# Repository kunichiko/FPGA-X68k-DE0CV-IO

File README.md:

# FPGA-X68k I/O Board for DE0-CV

詳しい使い方は [Wiki](https://github.com/kunichiko/FPGA-X68k-DE0CV-IO/wiki) を参照してください。

# License

This repository is published under CC BY-NC (Creative Commons Attribution-NonCommercial 4.0 International Public License).

本リポジトリはクリエイティブコモンズの CC BY-NC ライセンスの元に公開します。

本リポジトリには私が作成したもの以外に、第三者が権利を持つソフトウェア等(PCBフットプリントライブラリなど)が含まれています。CC BY-NCライセンスの元で再頒布しても問題がないように注意しておりますが、もし頒布条件などが満たされないものが含まれていた場合はご連絡ください。

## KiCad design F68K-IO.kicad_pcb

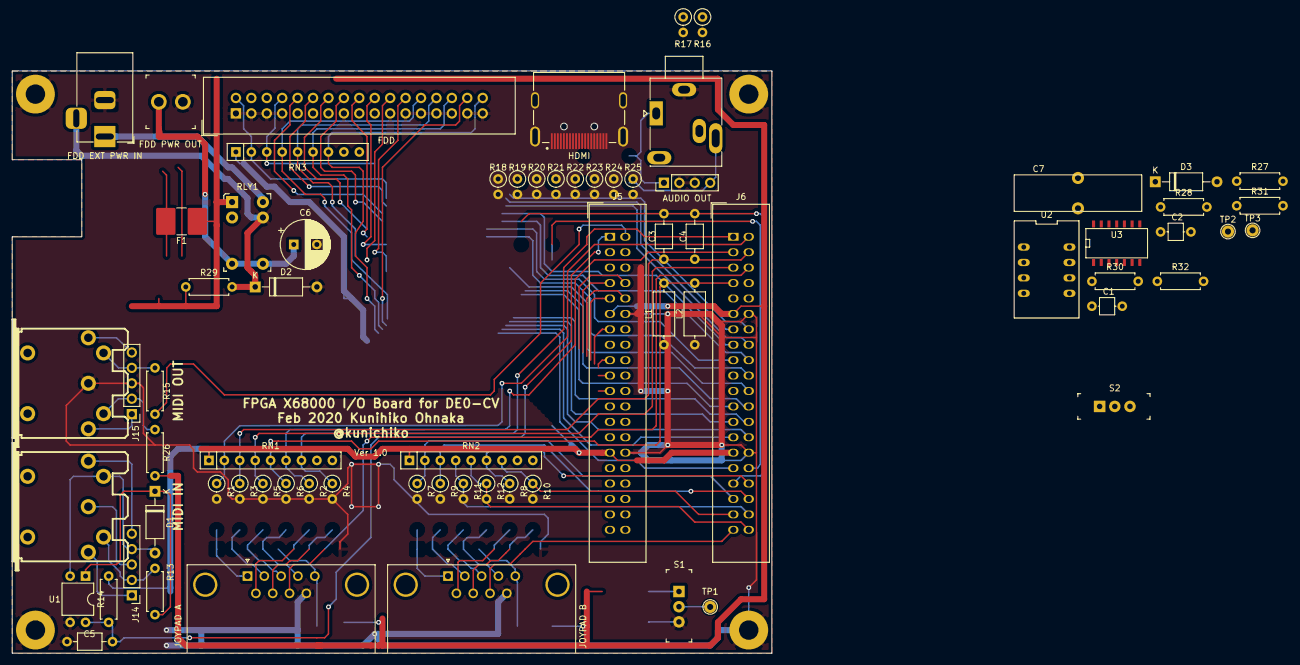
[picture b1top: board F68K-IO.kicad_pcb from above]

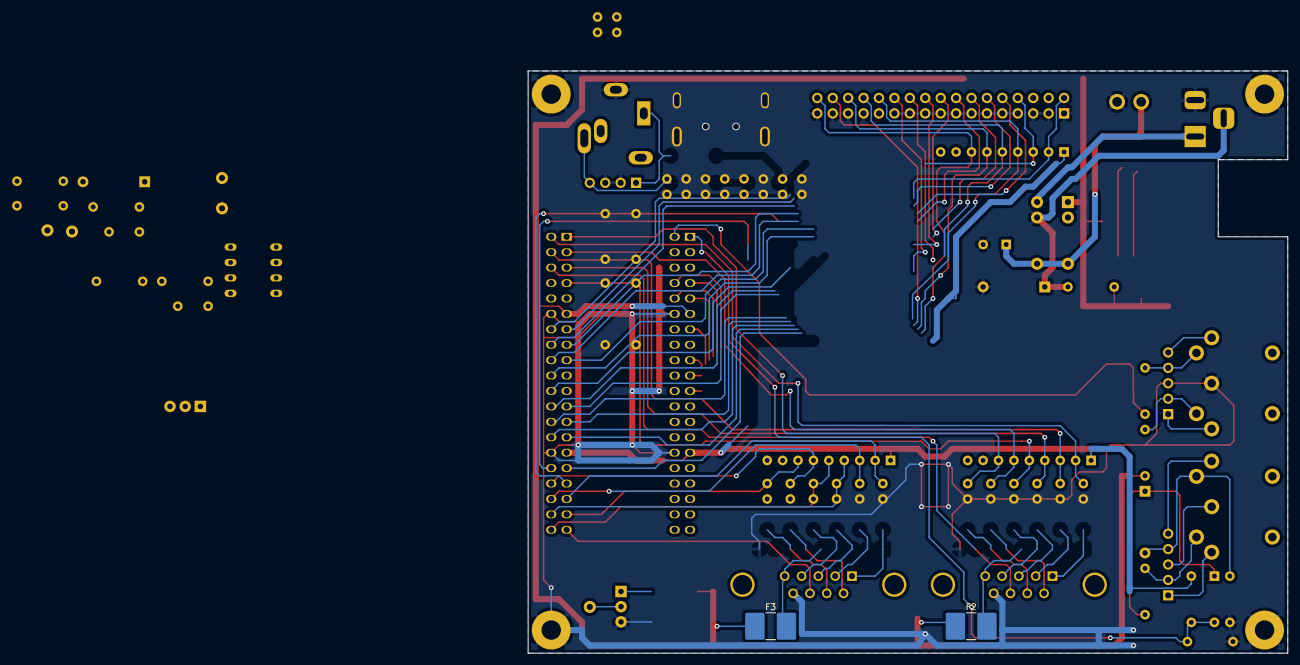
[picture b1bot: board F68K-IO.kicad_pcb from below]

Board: 2 copper layers, 125.1 x 95.9 mm, 77 parts (2 on the bottom side), 93 nets.

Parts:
C1, C2: 1000pF; C_Axial_L3.8mm_D2.6mm_P5.00mm_Horizontal
C3: 10μ; C_Axial_L3.8mm_D2.6mm_P7.50mm_Horizontal
C4: 0.33μ; C_Axial_L3.8mm_D2.6mm_P7.50mm_Horizontal
C5: 0.1μ; C_Axial_L3.8mm_D2.6mm_P7.50mm_Horizontal
C6: 220u; CP_Radial_D8.0mm_P3.80mm
C7: 1F 5.5V; SuperCapacitor_SE-SR5-D105VYV
D1, D2, D3: D; D_A-405_P10.16mm_Horizontal
F1, F2, F3: Fuse; Fuse_2816_7142Metric_Pad3.20x4.45mm_HandSolder
H1, H2, H3, H4: MountingHole_Pad; MountingHole_3.2mm_M3_Pad
J1: JOYPAD A; DSUB-9_Male_Horizontal_P2.77x2.84mm_EdgePinOffset9.90mm_Hou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
J2: AUDIO OUT; Jack_3.5mm_Ledino_KB3SPRS_Horizontal
J3: JOYPAD B; DSUB-9_Male_Horizontal_P2.77x2.84mm_EdgePinOffset9.90mm_Hou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
J4: FDD; IDC-Header_2x17_P2.54mm_Vertical
J5: GPIO 0; IDC-Header_2x20_P2.54mm_Vertical_OvalPad
J6: GPIO 1; IDC-Header_2x20_P2.54mm_Vertical_OvalPad
J8: Conn_01x04_Male; PinHeader_1x04_P2.54mm_Vertical
J10: MIDI IN; din-5
J11: MIDI OUT; din-5
J12: HDMI; TE_2-1747981-3
J14: MIDI IN (Alt); PinHeader_1x05_P2.54mm_Vertical
J15: MIDI OUT (Alt); PinHeader_1x05_P2.54mm_Vertical
J16: FDD EXT PWR IN; BarrelJack_Horizontal
J17: FDD PWR OUT; PinHeader_1x2_P3.96mm_Drill1.6mm
L1, L2: 10μ; L_Axial_L7.0mm_D3.3mm_P10.16mm_Horizontal_Fastron_MICC
R1, R2, R3, R4, R5, R6, R7, R8, R9, R10, R11, R12: 1k; R_Axial_DIN0207_L6.3mm_D2.5mm_P2.54mm_Vertical
R13, R14, R15, R26, R27, R28, R29, R30: 220; R_Axial_DIN0207_L6.3mm_D2.5mm_P7.62mm_Horizontal
R16, R17: 1.8k; R_Axial_DIN0207_L6.3mm_D2.5mm_P2.54mm_Vertical
R18, R19, R20, R21, R22, R23, R24, R25: 270; R_Axial_DIN0207_L6.3mm_D2.5mm_P2.54mm_Vertical
R31, R32: 1.8k; R_Axial_DIN0207_L6.3mm_D2.5mm_P7.62mm_Horizontal
RLY1: G5V-1-DC5; Relay_THT_G5V-1
RN1, RN2, RN3: 4.7k; R_Array_SIP9
S1, S2: EG1218; Switch_Slide_11.6x4mm_EG1218
TP1, TP2, TP3: TestPoint; TestPoint_THTPad_D2.0mm_Drill1.0mm
U1: TLP785; DIP-4_W7.62mm
U2: AE-RX-8025NB
U3: RX-8025SA; SOIC-14_N

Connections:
+3V3: J5.29, J6.29, R14.1, R31.1, R32.1, RN1.1, RN2.1, RN3.1
+5V: D3.2, F1.1, F2.1, F3.1, J5.11, J6.11, R16.2, R17.2, R26.2, R27.1, R28.1, R29.1, R30.1, RLY1.6
/AUDIO_L: J6.33, L1.2
/AUDIO_R: J6.32, L2.2
/FDD2: J4.2, J6.13, RN3.2
/FDD8: J4.8, J6.14, RN3.3
/FDD10: J4.10, J6.15
/FDD12: J4.12, J6.16
/FDD14: J4.14, J6.17
/FDD16: J4.16, J6.18
/FDD18: J4.18, J6.20
/FDD20: J4.20, J6.22
/FDD22: J4.22, J6.23
/FDD24: J4.24, J6.24
/FDD26: J4.26, J6.25, RN3.4
/FDD28: J4.28, J6.26, RN3.5
/FDD30: J4.30, J6.27, RN3.6
/FDD32: J4.32, J6.28
/FDD34: J4.34, J6.31, RN3.7
/HDMI_1_D2+: J12.1, R18.1
/HDMI_3_D2-: J12.3, R19.1
/HDMI_4_D1+: J12.4, R20.1
/HDMI_6_D1-: J12.6, R21.1
/HDMI_7_D0+: J12.7, R22.1
/HDMI_9_D0-: J12.9, R23.1
/HDMI_10_CK+: J12.10, R24.1
/HDMI_12_CK-: J12.12, R25.1
/HDMI_15_SCL: J12.15, R17.1
/HDMI_16_SDA: J12.16, R16.1
/HDMI_18_5V: F1.2, J12.18
/HDMI_CK+: J5.19, R24.2
/HDMI_CK-: J5.21, R25.2
/HDMI_D0+: J5.17, R22.2
/HDMI_D0-: J5.13, R23.2
/HDMI_D1+: J5.9, R20.2
/HDMI_D1-: J5.10, R21.2
/HDMI_D2+: J5.7, R18.2
/HDMI_D2-: J5.8, R19.2
/I2C_SCL: J6.10, R31.2, U2.6, U3.2
/I2C_SDA: J6.8, R32.2, U2.5, U3.13
/JOYAPD-A-DSUB_2: J6.4, R3.1, RN1.3
/JOYAPD-A-DSUB_3: J6.5, R5.1, RN1.4
/JOYAPD-A-DSUB_4: J6.7, R6.1, RN1.5
/JOYAPD-A-DSUB_6: J6.3, R2.1, RN1.6
/JOYAPD-A-DSUB_8: J1.8, J6.6
/JOYAPD-B-DSUB_1: J6.35, R7.1, RN2.2
/JOYAPD-B-DSUB_2: J6.36, R9.1, RN2.3
/JOYAPD-B-DSUB_3: J6.38, R11.1, RN2.4
/JOYAPD-B-DSUB_4: J6.40, R12.1, RN2.5
/JOYAPD-B-DSUB_6: J6.34, R8.1, RN2.6
/JOYAPD-B-DSUB_7: J6.37, R10.1, RN2.7
/JOYAPD-B-DSUB_8: J3.8, J6.39
/JOYPAD-A-DSUB_1: J6.2, R1.1, RN1.2
/JOYPAD-A-DSUB_7: J6.1, R4.1, RN1.7
/MIDI_IN: C5.1, J5.1, R14.2, U1.4
/MIDI_OUT: J11.5, J15.4, R15.1
GND: C1.2, C2.2, C5.2, C6.2, C7.2, D2.2, H1.1, H2.1, H3.1, H4.1, J1.9, J2.S, J3.9, J4.1, J4.3, J4.5, J4.7, J4.9, J4.11, J4.13, J4.15, J4.17, J4.19, J4.21, J4.23, J4.25, J4.27, J4.29, J4.31, J4.33, J5.12, J5.30, J6.12, J6.30, J8.2, J8.3, J11.2, J12.2, J12.5, J12.8, J12.11, J12.17, J15.3, J16.2, J17.2, RLY1.9, S1.3, S2.3, U1.3, U2.4, U3.11
unnamed: C1.1, C3.1, J2.T, J8.1
unnamed: C2.1, C4.1, J2.R, J8.4
unnamed: C3.2, L1.1
unnamed: C4.2, L2.1
unnamed: C6.1, J17.1, RLY1.1, RLY1.10
unnamed: C7.1, D3.1, U2.8, U3.6
unnamed: D1.1, R13.2, U1.1
unnamed: D1.2, J10.5, J14.4, U1.2
unnamed: D2.1, J16.3, R27.2, R28.2, R29.2, R30.2, RLY1.2
unnamed: F2.2, J1.5
unnamed: F3.2, J3.5
unnamed: J1.1, R1.2
unnamed: J1.2, R3.2
unnamed: J1.3, R5.2
unnamed: J1.4, R6.2
unnamed: J1.6, R2.2
unnamed: J1.7, R4.2
unnamed: J3.1, R7.2
unnamed: J3.2, R9.2
unnamed: J3.3, R11.2
unnamed: J3.4, R12.2
unnamed: J3.6, R8.2
unnamed: J3.7, R10.2
unnamed: J5.2, R15.2
unnamed: J6.9, S2.2
unnamed: J10.1, J14.1
unnamed: J10.2, J14.3
unnamed: J10.3, J14.5
unnamed: J10.4, J14.2, R13.1
unnamed: J11.1, J15.1
unnamed: J11.3, J15.5
unnamed: J11.4, J15.2, R26.1
unnamed: J16.1, RLY1.5
unnamed: S1.1, TP3.1
unnamed: S1.2, TP1.1
unnamed: S2.1, TP2.1

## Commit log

2020-03-01 Initial version (first PCB order version)
2020-03-01 Add LICENSE and README.
2020-03-01 Fix JOYPAD signal pull-up voltage from 5V to 3.3V.
2020-03-01 Arrange dependency libraries.
2020-03-14 Fix some connection failures.
    * Change MIDI IN signal pull-up voltage from 5V to 3.3V
    * Flip HDMI D0+ and D0-
2020-03-20 Update component's parameters for 1st delivery.
2020-07-04 Work in progress
